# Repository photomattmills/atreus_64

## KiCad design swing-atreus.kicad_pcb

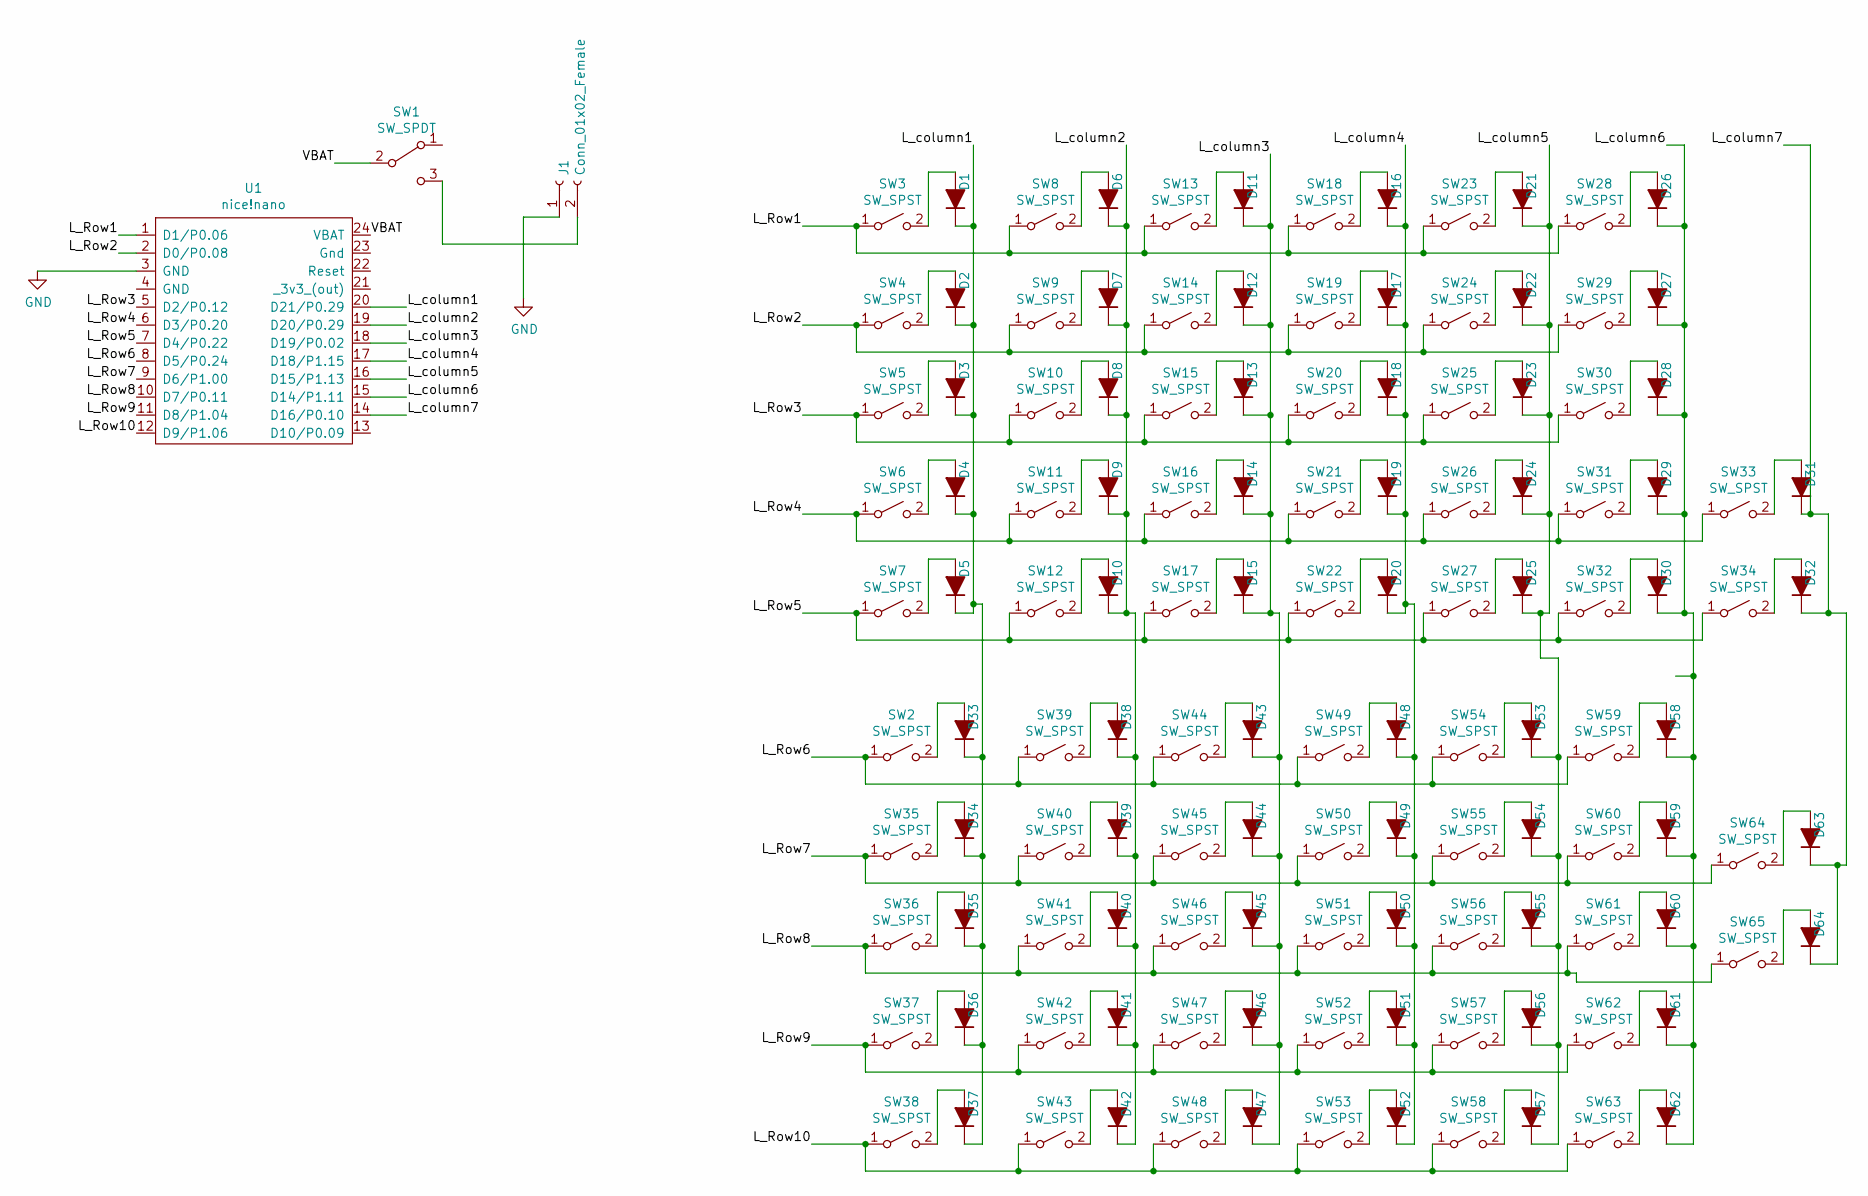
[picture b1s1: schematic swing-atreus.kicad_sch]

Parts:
D1, D2, D3, D4, D5, D6, D7, D8, D9, D10, D11, D12, D13, D14, D15, D16, D17, D18, D19, D20, D21, D22, D23, D24, D25, D26, D27, D28, D29, D30, D31, D32, D33, D34, D35, D36, D37, D38, D39, D40, D41, D42, D43, D44, D45, D46, D47, D48, D49, D50, D51, D52, D53, D54, D55, D56, D57, D58, D59, D60, D61, D62, D63, D64: D0; D_SOD-123
J1: Conn_01x02_Female; JST_PH_S2B-PH-SM4-TB_1x02-1MP_P2.00mm_Horizontal
SW1: SW_SPDT; EQZ1K2-switch
SW2, SW3, SW4, SW5, SW6, SW7, SW8, SW9, SW10, SW11, SW12, SW13, SW14, SW15, SW16, SW17, SW18, SW19, SW20, SW21, SW22, SW23, SW24, SW25, SW26, SW27, SW28, SW29, SW30, SW31, SW32, SW33, SW34, SW35, SW36, SW37, SW38, SW39, SW40, SW41, SW42, SW43, SW44, SW45, SW46, SW47, SW48, SW49, SW50, SW51, SW52, SW53, SW54, SW55, SW56, SW57, SW58, SW59, SW60, SW61, SW62, SW63, SW64, SW65: SW_SPST; SW_Kailh_Choc_V1V2_double
U1: nice!nano

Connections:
/L_Row1: SW3.1 (A), SW8.1 (A), SW13.1 (A), SW18.1 (A), SW23.1 (A), SW28.1 (A), U1.1 (D1/P0.06)
/L_Row2: SW4.1 (A), SW9.1 (A), SW14.1 (A), SW19.1 (A), SW24.1 (A), SW29.1 (A), U1.2 (D0/P0.08)
/L_Row3: SW5.1 (A), SW10.1 (A), SW15.1 (A), SW20.1 (A), SW25.1 (A), SW30.1 (A), U1.5 (D2/P0.12)
/L_Row4: SW6.1 (A), SW11.1 (A), SW16.1 (A), SW21.1 (A), SW26.1 (A), SW31.1 (A), SW33.1 (A), U1.6 (D3/P0.20)
/L_Row5: SW7.1 (A), SW12.1 (A), SW17.1 (A), SW22.1 (A), SW27.1 (A), SW32.1 (A), SW34.1 (A), U1.7 (D4/P0.22)
/L_Row6: SW2.1 (A), SW39.1 (A), SW44.1 (A), SW49.1 (A), SW54.1 (A), SW59.1 (A), U1.8 (D5/P0.24)
/L_Row7: SW35.1 (A), SW40.1 (A), SW45.1 (A), SW50.1 (A), SW55.1 (A), SW60.1 (A), SW64.1 (A), U1.9 (D6/P1.00)
/L_Row8: SW36.1 (A), SW41.1 (A), SW46.1 (A), SW51.1 (A), SW56.1 (A), SW61.1 (A), SW65.1 (A), U1.10 (D7/P0.11)
/L_Row9: SW37.1 (A), SW42.1 (A), SW47.1 (A), SW52.1 (A), SW57.1 (A), SW62.1 (A), U1.11 (D8/P1.04)
/L_Row10: SW38.1 (A), SW43.1 (A), SW48.1 (A), SW53.1 (A), SW58.1 (A), SW63.1 (A), U1.12 (D9/P1.06)
/L_column1: D1.1 (K), D2.1 (K), D3.1 (K), D4.1 (K), D5.1 (K), D33.1 (K), D34.1 (K), D35.1 (K), D36.1 (K), D37.1 (K), U1.20 (D21/P0.29)
/L_column2: D6.1 (K), D7.1 (K), D8.1 (K), D9.1 (K), D10.1 (K), D38.1 (K), D39.1 (K), D40.1 (K), D41.1 (K), D42.1 (K), U1.19 (D20/P0.29)
/L_column3: D11.1 (K), D12.1 (K), D13.1 (K), D14.1 (K), D15.1 (K), D43.1 (K), D44.1 (K), D45.1 (K), D46.1 (K), D47.1 (K), U1.18 (D19/P0.02)
/L_column4: D16.1 (K), D17.1 (K), D18.1 (K), D19.1 (K), D20.1 (K), D48.1 (K), D49.1 (K), D50.1 (K), D51.1 (K), D52.1 (K), U1.17 (D18/P1.15)
/L_column5: D21.1 (K), D22.1 (K), D23.1 (K), D24.1 (K), D25.1 (K), D53.1 (K), D54.1 (K), D55.1 (K), D56.1 (K), D57.1 (K), U1.16 (D15/P1.13)
/L_column6: D26.1 (K), D27.1 (K), D28.1 (K), D29.1 (K), D30.1 (K), D58.1 (K), D59.1 (K), D60.1 (K), D61.1 (K), D62.1 (K), U1.15 (D14/P1.11)
/L_column7: D31.1 (K), D32.1 (K), D63.1 (K), D64.1 (K), U1.14 (D16/P0.10)
/VBAT: SW1.2 (B), U1.24 (VBAT)
GND: J1.1, U1.3 (GND)
unnamed: D1.2 (A), SW3.2 (B)
unnamed: D2.2 (A), SW4.2 (B)
unnamed: D3.2 (A), SW5.2 (B)
unnamed: D4.2 (A), SW6.2 (B)
unnamed: D5.2 (A), SW7.2 (B)
unnamed: D6.2 (A), SW8.2 (B)
unnamed: D7.2 (A), SW9.2 (B)
unnamed: D8.2 (A), SW10.2 (B)
unnamed: D9.2 (A), SW11.2 (B)
unnamed: D10.2 (A), SW12.2 (B)
unnamed: D11.2 (A), SW13.2 (B)
unnamed: D12.2 (A), SW14.2 (B)
unnamed: D13.2 (A), SW15.2 (B)
unnamed: D14.2 (A), SW16.2 (B)
unnamed: D15.2 (A), SW17.2 (B)
unnamed: D16.2 (A), SW18.2 (B)
unnamed: D17.2 (A), SW19.2 (B)
unnamed: D18.2 (A), SW20.2 (B)
unnamed: D19.2 (A), SW21.2 (B)
unnamed: D20.2 (A), SW22.2 (B)
unnamed: D21.2 (A), SW23.2 (B)
unnamed: D22.2 (A), SW24.2 (B)
unnamed: D23.2 (A), SW25.2 (B)
unnamed: D24.2 (A), SW26.2 (B)
unnamed: D25.2 (A), SW27.2 (B)
unnamed: D26.2 (A), SW28.2 (B)
unnamed: D27.2 (A), SW29.2 (B)
unnamed: D28.2 (A), SW30.2 (B)
unnamed: D29.2 (A), SW31.2 (B)
unnamed: D30.2 (A), SW32.2 (B)
unnamed: D31.2 (A), SW33.2 (B)
unnamed: D32.2 (A), SW34.2 (B)
unnamed: D33.2 (A), SW2.2 (B)
unnamed: D34.2 (A), SW35.2 (B)
unnamed: D35.2 (A), SW36.2 (B)
unnamed: D36.2 (A), SW37.2 (B)
unnamed: D37.2 (A), SW38.2 (B)
unnamed: D38.2 (A), SW39.2 (B)
unnamed: D39.2 (A), SW40.2 (B)
unnamed: D40.2 (A), SW41.2 (B)
unnamed: D41.2 (A), SW42.2 (B)
unnamed: D42.2 (A), SW43.2 (B)
unnamed: D43.2 (A), SW44.2 (B)
unnamed: D44.2 (A), SW45.2 (B)
unnamed: D45.2 (A), SW46.2 (B)
unnamed: D46.2 (A), SW47.2 (B)
unnamed: D47.2 (A), SW48.2 (B)
unnamed: D48.2 (A), SW49.2 (B)
unnamed: D49.2 (A), SW50.2 (B)
unnamed: D50.2 (A), SW51.2 (B)
unnamed: D51.2 (A), SW52.2 (B)
unnamed: D52.2 (A), SW53.2 (B)
unnamed: D53.2 (A), SW54.2 (B)
unnamed: D54.2 (A), SW55.2 (B)
unnamed: D55.2 (A), SW56.2 (B)
unnamed: D56.2 (A), SW57.2 (B)
unnamed: D57.2 (A), SW58.2 (B)
unnamed: D58.2 (A), SW59.2 (B)
unnamed: D59.2 (A), SW60.2 (B)
unnamed: D60.2 (A), SW61.2 (B)
unnamed: D61.2 (A), SW62.2 (B)
unnamed: D62.2 (A), SW63.2 (B)
unnamed: D63.2 (A), SW64.2 (B)
unnamed: D64.2 (A), SW65.2 (B)
unnamed: J1.2, SW1.3 (C)

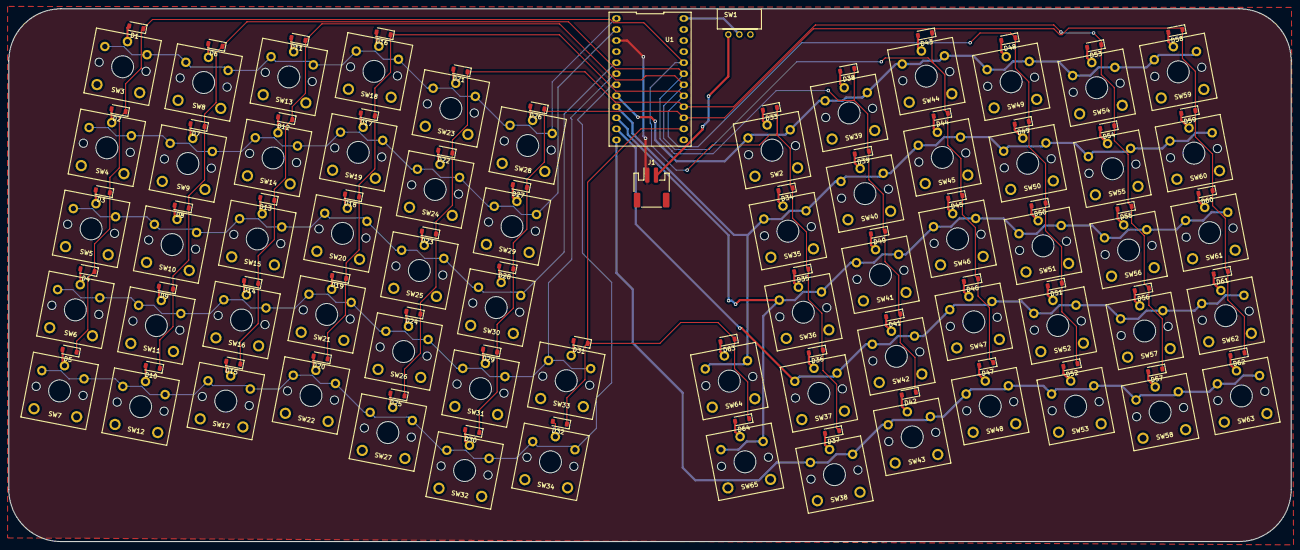
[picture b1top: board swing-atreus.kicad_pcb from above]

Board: 2 copper layers, 295.2 x 122.6 mm, 131 parts (0 on the bottom side), 84 nets.

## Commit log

2022-11-20 initial commit, sent to fab
2024-05-02 update to single board design
2024-05-02 add copper fills
